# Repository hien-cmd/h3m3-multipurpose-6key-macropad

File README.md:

# H3M3 - THE multi-purpose 6 key macro pad
This is a 6 key macro pad with 6 programmable keys, 3 being hotswap mechanical switches for casual work and the other 3 being magnetic switches for with adjustable sensitivity for gaming.

## Features
- 3 hotswap mechanical switches
- 3 interchangable magnetic switches
- Fully programmable keys and firmware(now can all be modified in a config.json file!)
- Small form factor
- Open source hardware and firmware

## BOM

## Tools needed
- Soldering iron and a bit of solder
- Hot glue gun and a bit of glue
- 3D printer

## Firmware
- code.py, built using CircuitPython and KMK

## Schematic

## PCB

## 3D-printable case

## Prerequisites
-Has all the hardware needed
-Has the 3d printed case, keycaps and the PCB

## Assembly instructions
1. Solder hotswap sockets onto pcb
2. Solder RP2040-Zero headers in if you haven't yet, then solder RP2040-ZERO to PCB
3. Solder in Hall Effect sensors so it sits on the holes in each magnetic switch slot on the PCB
4. Put the PCB into the case
5. Fit the 3 mechanical switches through the casing and fit the pins into the hotswap sockets, so the PCB sits where it should be, then fit the magnetic switches in
6. Put the keycaps on each switch
7. Put the upper half onto the bottom casing, you can glue it together if you want but gravity already keeps it stable, personally I don't so i can quickly fix hardware issues

## Firmware installation
1. Install CircuitPython on the RP2040-Zero:
    1. Plug the RP2040-Zero into your computer, a new storage disk should appear
    2. Download the CircuitPython file here: https://circuitpython.org/board/waveshare_rp2040_zero/
    3. Drag that file into the storage disk, the disk should rename itself into "CIRCUITPY"
2. Download the full adafruit_hid library here: https://github.com/adafruit/Adafruit_CircuitPython_HID
3. Download the full kmk library here: https://github.com/KMKfw/kmk_firmware
4. Drag ONLY the "adafruit_hid" and "kmk" folders inside their corresponding folders and put it in the "lib" folder in the "CIRCUITPY" disk
5. Drag the provided "code.py" file into the "CIRCUITPY" disk and REPLACE the existing code.py file
6. Drag the config.json file into the "CIRCUITPY" disk

## Default keymap(m=mechanical switch, a=analog/magnetic/hall effect switches)
M1 - a
M2 - b
M3 - ESC
A1 - z
A2 - x
A3 - c

## Programming and customization guide

### How the magnetic switches work
Each magnetic switch is read as an analog voltage through a Hall Effect sensor. Rather than a single fixed on/off point, the firmware measures each sensor's own resting voltage at boot, then watches for it to dip by a set amount when a magnet gets close. This means switch to switch differences in magnet strength or sensor tolerance are absorbed automatically, and every tuning value below is a depth or delta relative to that switch's own resting point rather than an absolute voltage.

### config.json structure
config.json has three top level sections:
- "mechanical_keys": a list of 3 key names for the mechanical switches, in the order M1, M2, M3
- "hall_effect": one entry per magnetic switch (GP27, GP28, GP29), each with a "key" name and, optionally, its own overrides for any of the per switch tuning values below
- "tuning": the global defaults used by any magnetic switch that doesn't set its own override, plus a few board wide settings
  
### Per switch tuning
Inside a switch's entry under "hall_effect", any of these can be set individually for that switch. Leave one out and it falls back to the matching value in "tuning" instead:

- "actuation_depth": how far, in volts, the voltage has to drop from that switch's own resting point before it registers as pressed. This is the main sensitivity knob, lower means a lighter, earlier press
- "hysteresis": the gap, in volts, between the press point and the release point, only used when "rapid_trigger" is off. Keeps a switch sitting right at the threshold from chattering
- "rapid_trigger": turns rapid trigger on or off for this switch on its own, so you can mix and match. On means fast reset for gaming, off means the key stays held down until you physically let it back up, which is what you want for a hold to repeat key
- "rt_press_delta": with "rapid_trigger" on, how far the voltage has to push back down from the highest point reached since release before it re-presses
- "rt_release_delta": with "rapid_trigger" on, how far the voltage has to lift back up from the deepest point reached since pressing before it releases
- "rest_v": the resting voltage to use for that switch if "auto_calibrate" is turned off
- "reject_v": that switch's fault floor, see the warning under board wide tuning below

### Board wide tuning
These live only in "tuning" and apply to every magnetic switch:

- "debug": prints resting voltage at boot and live readings a few times a second when true, off by default since it does slow the board down slightly
- "auto_calibrate": measures each switch's own resting voltage at boot instead of using a fixed "rest_v". Leave this on unless you have a specific reason not to
- "rapid_trigger": the default for every switch that doesn't set its own, turns on press and release based on direction of travel rather than a single fixed point, this is what makes the switches feel fast for gaming. Turn it off for simple, predictable single actuation behavior instead
- "filter_strength": how much incoming noise gets smoothed out, higher is smoother but slightly slower to react. 2 is a good starting point
- "reject_v": a fault floor, any reading below this is treated as a disconnected or malfunctioning sensor and the key is forced off. 

### Magnetic/Hall Effect switches calibration 
As mentioned in the properties list, rapid trigger and more advanced functions need fine tuning and proper calibration:
1. Set "debug" in config.json to "true" and save the file
2. Open a serial monitor such as Thonny or Terminal(I personally use Terminal's built-in screen function) at baud 115200
3. Note the resting value of each switch at boot
4. One by one press each magnetic switch and note the voltage when it is pressed.
5. The difference between the resting voltage and the one where it's fully pressed is its full travel. A good "actuation_depth" value for each switch is about a third to half of that value, adjust to however you want it. Here's some reference ranges:
- Small actuation_depth (0.05 to 0.10) very sensitive
- Medium (0.15), about halfway down
- Large (0.25 and up) deeper presses. 
6. If the switches starts pressing on its own, remove the switches in that slot immediatly and raise its actuation depth
7. Set "debug" back to false once you're done
Or if you want a quicker way(however not that precise) you can just raise or lower the preset actuation depth and have a feel for it.

### Debug functions
When "debug" is set to "true" in the config.json, it prints each magnetic switch's resting voltage at boot and then its live current voltage. This can be seen with a serial monitor such as Terminal's built in screen function to calibrate actuation depth. Leave it off if you aren't calibrating it because it does make a slightly less reactive.

### Mechanical switches properties
keyboard.matrix:
    - pins: this defines the pins where the mechanical switches are placed.
    - value_when_pressed: this is the value when the key is pressed. It is determined by the microcontroller's pull up resistor, which registers a constant HIGH/True(3.3V) until the mechanical switch is pressed and join the pin with GND, which pulls it down to Low/False(0V). This can be changed(but in most cases don't).
keyboard.keymap: this defines what is typed when a keystroke is registered, can be changed at line 100

##Credits
-Keycaps made by this parametric model maker: https://makerworld.com/en/makerlab/parametricModelMaker?designId=2182165&from=model_page&modelName=Keycap_customizable_v1_template.scad&protected=true&unikey=a6cd5a4e-c0e8-4990-b4b3-d559a98cbdf8
-Footprint for Kailh hotswap sockets: https://github.com/kiswitch/keyswitch-kicad-library

## AI usage in this project
Only some parts of the code was written by AI, primarily to fix bugs and the schematic, PCB, 3d printable case is completely hand designed by me. All code is reviewed and modified by me. This README of course is made by me.

## Possible future improvements
    -RGB lighting
    -Rotary encoder slot 

## License
MIT License

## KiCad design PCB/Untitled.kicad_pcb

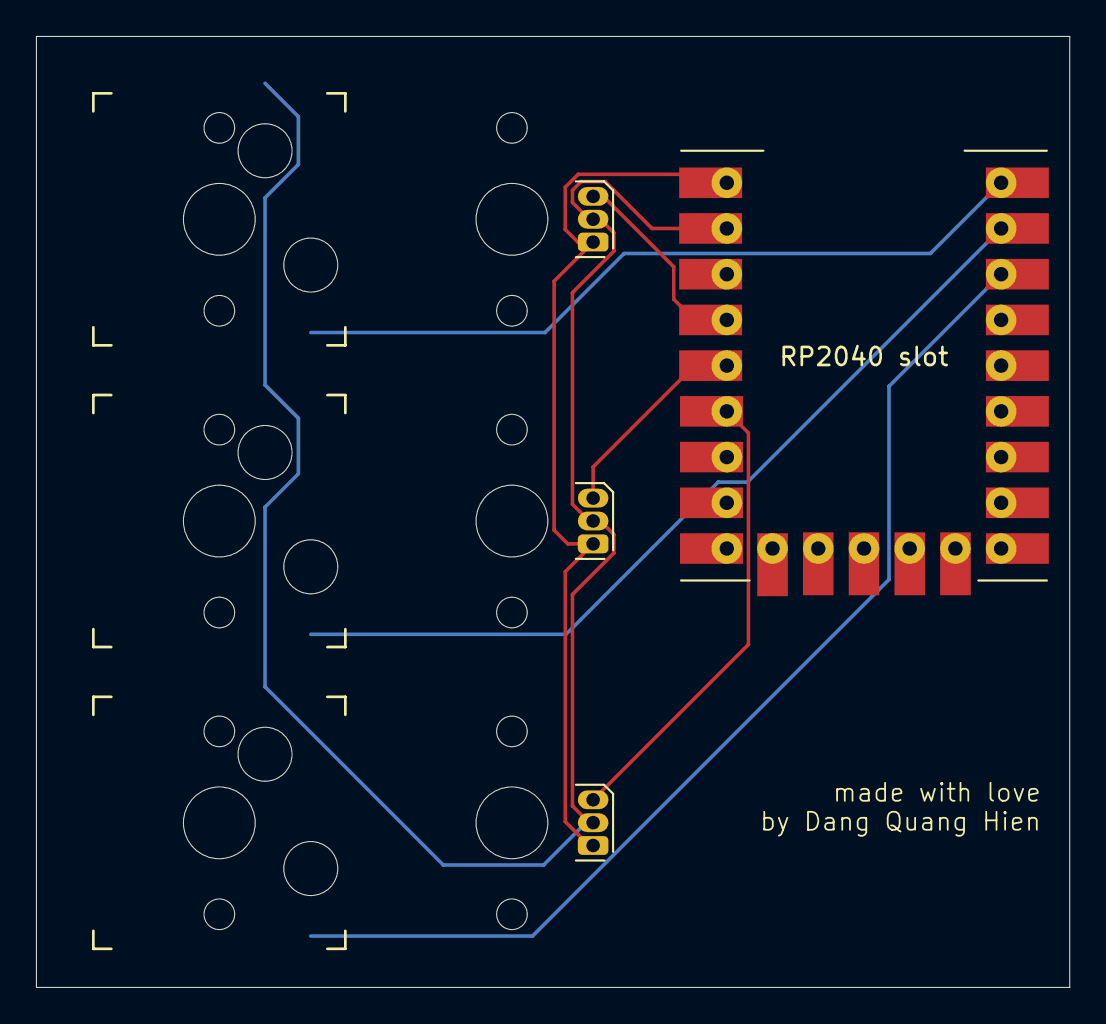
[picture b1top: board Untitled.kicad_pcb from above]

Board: 2 copper layers, 57.4 x 52.8 mm, 7 parts (0 on the bottom side), 8 nets.

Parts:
RP2040 slot: RP2040-Zero; RP2040 Zero
SW1, SW2, SW3: SW_Push; Kailh_socket_MX
U1, U2, U3: A1301xUA; TO-92S

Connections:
unnamed: RP2040 slot.2 (GND), SW1.2, SW2.2, SW3.2, U1.2 (GND), U2.2 (GND), U3.2 (GND)
unnamed: RP2040 slot.1 (5V), U1.1 (V_{CC}), U2.1 (V_{CC}), U3.1 (V_{CC})
unnamed: RP2040 slot.4 (GP29), U1.3 (V_{OUT})
unnamed: RP2040 slot.5 (GP28), U2.3 (V_{OUT})
unnamed: RP2040 slot.6 (GP27), U3.3 (V_{OUT})
unnamed: RP2040 slot.10 (GP0), SW1.1
unnamed: RP2040 slot.11 (GP1), SW2.1
unnamed: RP2040 slot.12 (GP2), SW3.1
